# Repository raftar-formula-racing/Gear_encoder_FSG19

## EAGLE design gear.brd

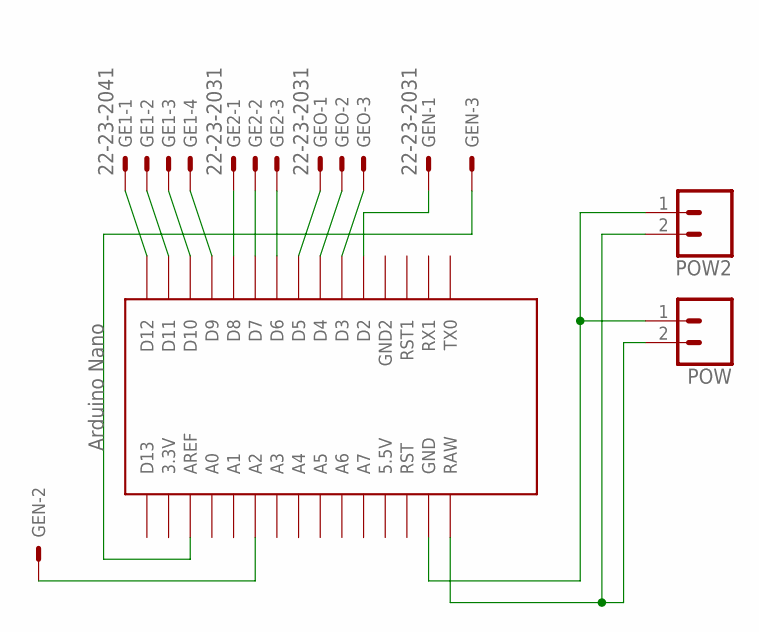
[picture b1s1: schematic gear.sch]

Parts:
GE1: 22-23-2041
GE2: 22-23-2031
GEN: 22-23-2031
GEO: 22-23-2031
POW, POW2: CONN_025MM; SCREWTERMINAL-5MM-2
U$1: NANO

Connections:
unnamed: GE1.1, U$1.D12
unnamed: GE1.2, U$1.D11
unnamed: GE1.3, U$1.D10
unnamed: GE1.4, U$1.D9
unnamed: GE2.1, U$1.D8
unnamed: GE2.2, U$1.D7
unnamed: GE2.3, U$1.D6
unnamed: GEO.1, U$1.D5
unnamed: GEO.2, U$1.D4
unnamed: GEO.3, U$1.D3
unnamed: POW.1, POW2.1, U$1.GND
unnamed: POW.2, POW2.2, U$1.RAW
unnamed: GEN.1, U$1.D2
unnamed: GEN.2, U$1.A2
unnamed: GEN.3, U$1.AREF

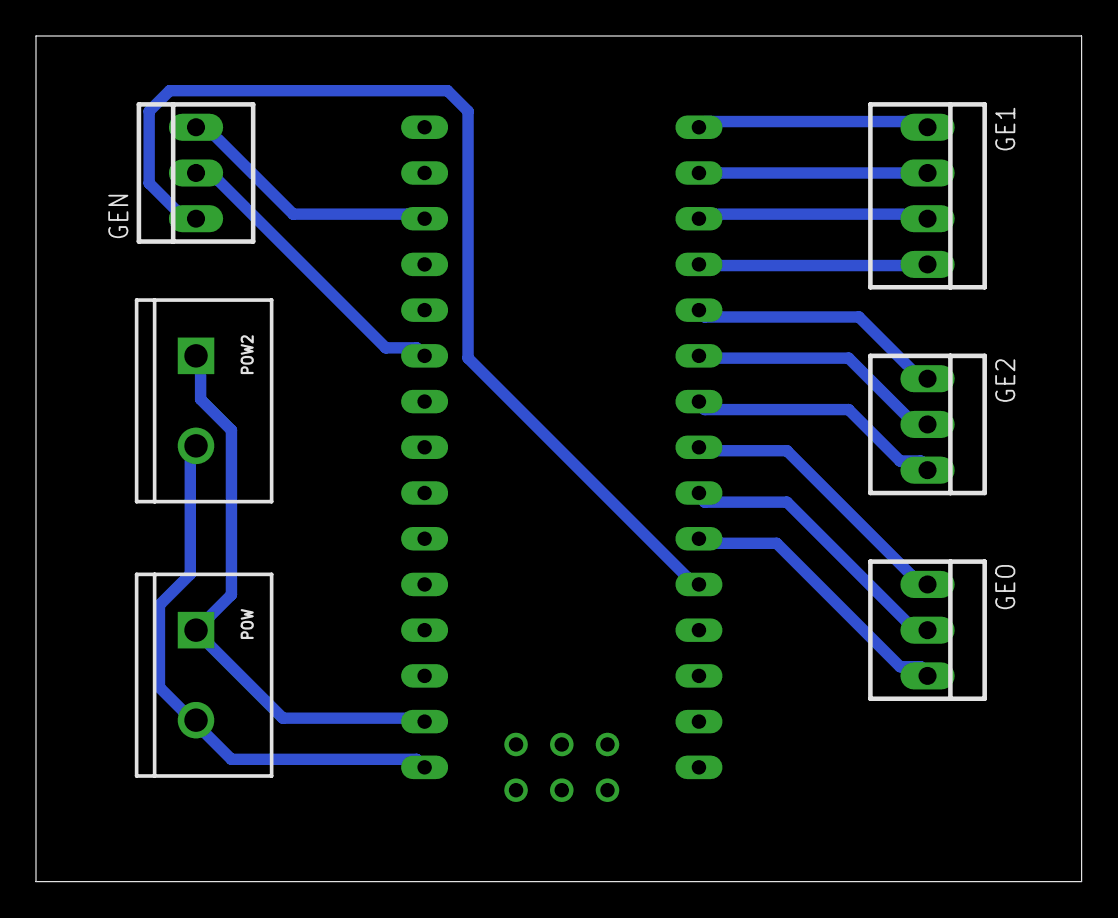
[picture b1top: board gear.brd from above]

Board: 2 copper layers, 58.1 x 47.0 mm, 7 parts (0 on the bottom side), 15 nets.

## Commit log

2019-09-06 Version 1 with less optimization
2019-09-06 Final Version Printed for FSG19

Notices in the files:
parts and their libraries:
SparkFun-Retired: Licensing: Creative Commons ShareAlike 4.0 International - https://creativecommons.org/licenses/by-sa/4.0
